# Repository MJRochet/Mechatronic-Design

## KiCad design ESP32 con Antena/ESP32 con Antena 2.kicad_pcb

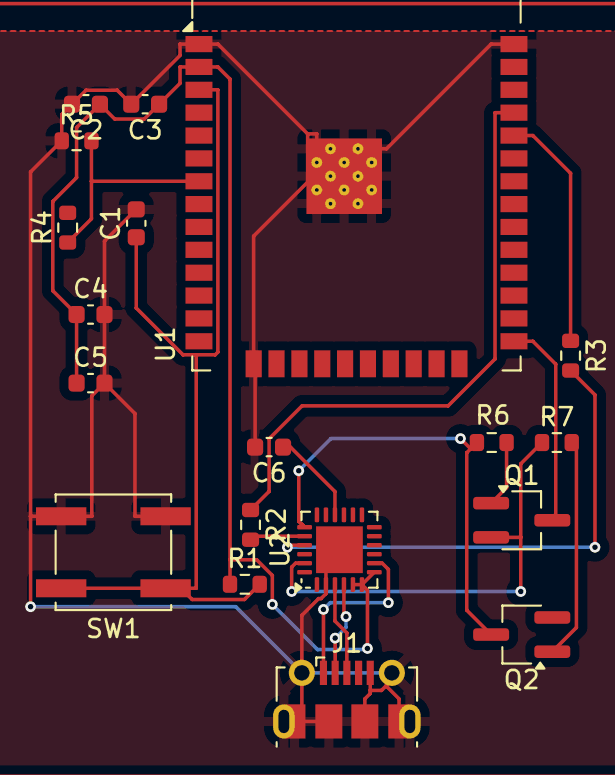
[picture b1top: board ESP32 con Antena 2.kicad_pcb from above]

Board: 2 copper layers, 19 parts (0 on the bottom side), 17 nets.

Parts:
C1, C3, C5: 10uF; C_0603_1608Metric
C2, C4: 100nF; C_0603_1608Metric
C6: 4.7uF; C_0603_1608Metric
J1: USB_B_Mini; USB_Micro-B_Molex-105017-0001
Q1, Q2: BC847; SOT-23W_Handsoldering
R1, R4, R5, R6, R7: 10K; R_0603_1608Metric
R2, R3: 470; R_0603_1608Metric
SW1: SW_Push_Dual; SW_Push_1P1T_NO_CK_KSC6xxJ
U1: ESP32-WROOM-32
U2: CP2104; QFN-24-1EP_4x4mm_P0.5mm_EP2.6x2.6mm

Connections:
+3.3V: C2.1, C3.1, C4.1, C5.1, R1.1, U1.2 (VDD), U2.5 (VIO), U2.6 (VDD), U2.7 (REGIN)
D+: J1.3 (D+), U2.3 (D+)
D-: J1.2 (D-), U2.4 (D-)
DTR: Q1.2 (E), R7.1, U2.23 (~DTR)
GND: C1.2, C2.2, C3.2, C4.2, C5.2, C6.2, J1.5 (GND), J1.6 (Shield), R5.1, SW1.1, U1.1 (GND), U1.15 (GND), U1.38 (GND), U1.39 (GND), U2.2 (GND), U2.25 (GND)
GPIO0: Q1.3 (C), U1.25 (IO0)
unnamed: Q1.1 (B), R6.2
unnamed: Q2.1 (B), R7.2
unnamed: C1.1, R1.2, SW1.2, U1.3 (EN)
unnamed: R4.1, R5.2, U1.7 (IO35)
unnamed: R3.1, U1.34 (RXD0/IO3)
unnamed: R2.1, U1.35 (TXD0/IO1)
unnamed: C6.1, U2.16 (VPP)
RTS: Q2.3 (C), R6.1, U2.19 (~RTS)
RX_CP: R2.2, U2.20 (RXD)
TX_CP: R3.2, U2.21 (TXD)
VBUS: J1.1 (VBUS), U2.8 (VBUS)

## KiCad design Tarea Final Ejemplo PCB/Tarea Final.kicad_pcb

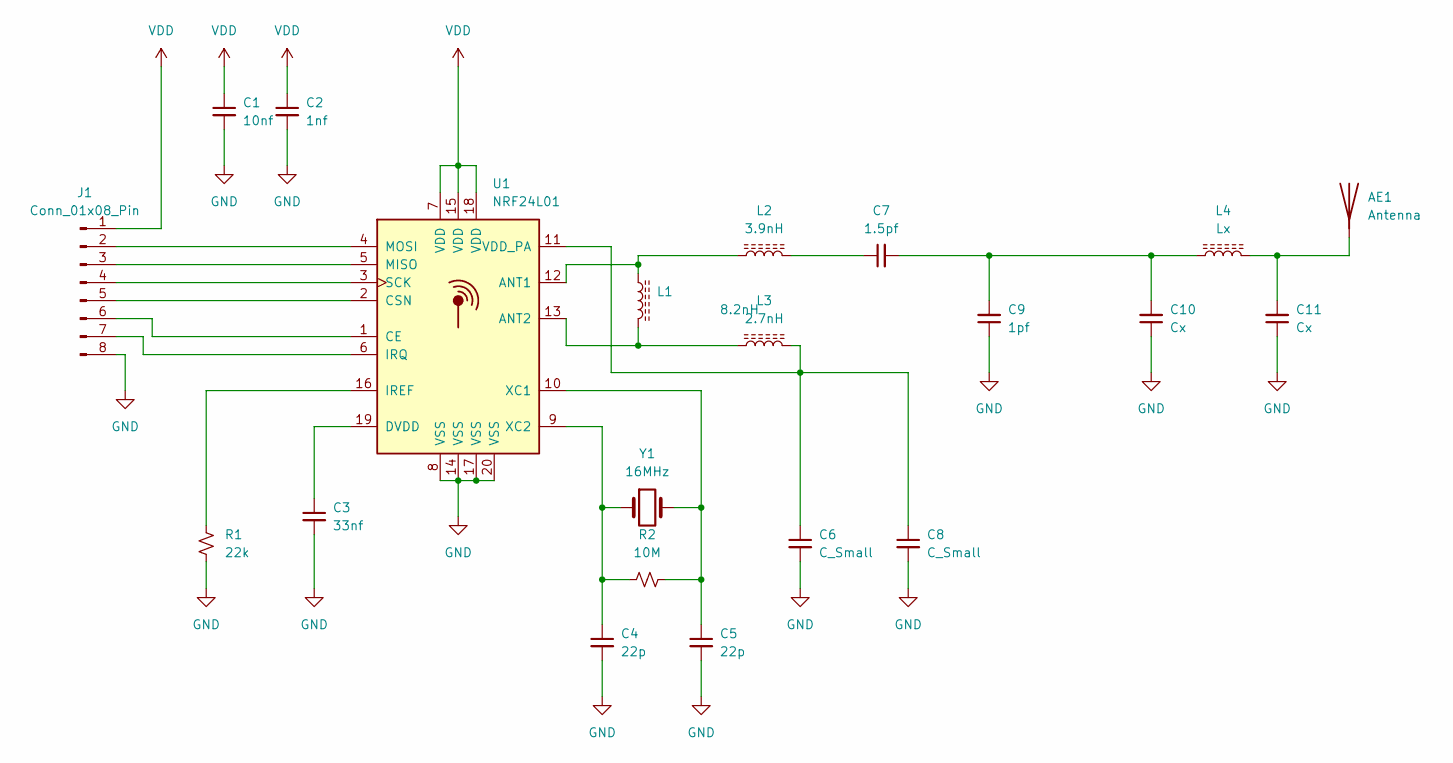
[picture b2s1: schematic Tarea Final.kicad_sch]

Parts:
AE1: Antenna; Texas_SWRA117D_2.4GHz_Right
C1: 10nf; C_0402_1005Metric
C2: 1nf; C_0402_1005Metric
C3: 33nf; C_0402_1005Metric
C4, C5: 22p; C_0402_1005Metric
C6, C8: C_Small; C_0402_1005Metric
C7: 1.5pf; C_0402_1005Metric
C9: 1pf; C_0402_1005Metric
C10, C11: Cx; C_0402_1005Metric
J1: Conn_01x08_Pin; Hirose_DF13-08P-1.25DSA_1x08_P1.25mm_Vertical
L1: 8.2nH; L_0402_1005Metric
L2: 3.9nH; L_0402_1005Metric
L3: 2.7nH; L_0402_1005Metric
L4: Lx; L_0402_1005Metric
R1: 22k; R_0402_1005Metric
R2: 10M; R_0402_1005Metric
U1: NRF24L01; QFN-20-1EP_4x4mm_P0.5mm_EP2.5x2.5mm
Y1: 16MHz; Crystal_SMD_3215-2Pin_3.2x1.5mm

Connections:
GND: C1.2, C2.2, C3.2, C4.2, C5.2, C6.2, C8.2, C9.1, C10.1, C11.1, J1.8, R1.2, U1.8 (VSS), U1.14 (VSS), U1.17 (VSS), U1.20 (VSS)
unnamed: AE1.1 (A), C11.2, L4.2
unnamed: C7.1, L2.2
unnamed: C7.2, C9.2, C10.2, L4.1
unnamed: J1.2, U1.4 (MOSI)
unnamed: J1.3, U1.5 (MISO)
unnamed: J1.4, U1.3 (SCK)
unnamed: J1.5, U1.2 (CSN)
unnamed: J1.6, U1.1 (CE)
unnamed: J1.7, U1.6 (IRQ)
unnamed: L1.1, L2.1, U1.12 (ANT1)
unnamed: L1.2, L3.1, U1.13 (ANT2)
unnamed: C3.1, U1.19 (DVDD)
unnamed: R1.1, U1.16 (IREF)
unnamed: C6.1, C8.1, L3.2, U1.11 (VDD_PA)
unnamed: C5.1, R2.2, U1.10 (XC1), Y1.2
unnamed: C4.1, R2.1, U1.9 (XC2), Y1.1
VDD: C1.1, C2.1, J1.1, U1.7 (VDD), U1.15 (VDD), U1.18 (VDD)

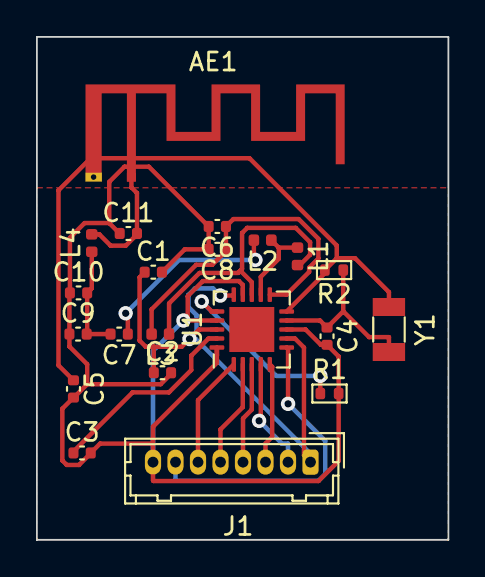
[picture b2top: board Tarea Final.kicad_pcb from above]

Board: 2 copper layers, 22.9 x 27.9 mm, 21 parts (0 on the bottom side), 18 nets.
